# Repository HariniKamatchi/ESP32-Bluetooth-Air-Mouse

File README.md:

# ESP32-Based Bluetooth Air Mouse Using MPU6050

A gesture-controlled wireless air mouse developed using an ESP32 microcontroller and MPU6050 motion sensor. The project explores an alternative approach to traditional computer input devices by translating hand movements into cursor control.

## 1. Project Overview

The Air Mouse is an embedded system designed to enable computer interaction through hand gestures rather than a conventional physical mouse.

The system uses the MPU6050, which integrates a 3-axis accelerometer and a 3-axis gyroscope, to capture hand movement and orientation. The ESP32 processes the sensor readings and supports wireless communication with a host computer.

An LDR-based input mechanism is also incorporated to detect gesture-based clicking.

The project combines motion sensing, embedded programming, wireless communication and custom PCB development to demonstrate gesture-based human-computer interaction.

## 2. Key Features

- Gesture-based cursor movement using MPU6050.
- ESP32-based embedded processing.
- 3-axis accelerometer and gyroscope data acquisition.
- I2C communication between ESP32 and MPU6050.
- LDR-based click detection.
- Serial data transmission for host-side visualization.
- Custom PCB design using KiCad.
- Compact and portable hardware architecture.

## 3. Hardware Components

| Component | Function |
|---|---|
| ESP32 Development Board | Main microcontroller |
| MPU6050 | Motion and orientation sensing |
| LDR | Gesture-based click detection |
| 56 kΩ Resistor | LDR voltage divider |
| Li-ion Battery | Portable power supply |
| TP4056 Module | Battery charging |
| Perfboard | Initial hardware implementation |
| Custom PCB | Hardware integration |

## 4. Software and Tools

- Arduino IDE
- Embedded C/C++
- Processing IDE
- KiCad PCB Design Suite
- Adafruit MPU6050 Library
- Adafruit Unified Sensor Library
- Wire Library
- Processing Serial Library

## 5. System Architecture

The system consists of three primary stages:

**1. Motion Sensing**

The MPU6050 captures hand movements and orientation using its accelerometer and gyroscope.

**2. Data Acquisition and Processing**

The ESP32 reads the sensor values through the I2C interface. Gyroscope readings are scaled to generate cursor movement values. The LDR input is used to determine the click state.

**3. Host-Side Visualization**

The ESP32 transmits the processed values through serial communication. A Processing application receives the data and visualizes cursor movement, click status and LDR readings.

### Data Communication Format

The ESP32 sends the following comma-separated data:

`gx,gy,click,ldrValue`

The data is transmitted at 115200 baud with a 50 ms sampling delay.

## 6. PCB Design

A custom Printed Circuit Board (PCB) was designed using **KiCad** to organize and integrate the electronic components.

The PCB design files are included in the repository.

The PCB development work includes:

- Circuit schematic design.
- PCB layout and routing.
- Component placement.
- Track routing and connectivity.
- PCB design visualization.

The repository includes the updated circular PCB layout. The earlier rectangular PCB design is documented in the original project report.

## 7. Repository Structure

```text
ESP32-Bluetooth-Air-Mouse/
│
├── Firmware/
│   └── Air_Mouse_ESP32.ino
│
├── Processing/
│   └── Air_Mouse_Processing.pde
│
├── PCB_Design/
│   ├── airmouse_embedded.kicad_pro
│   ├── airmouse_embedded.kicad_pcb
│   ├── airmouse_embedded.kicad_sch
│   ├── airmouse_embedded.net
│   └── README.md
│
├── Hardware/
│
├── Images/
│
├── Documentation/
│
├── README.md
└── LICENSE
```

## 8. Getting Started

### ESP32 Firmware Setup

1. Install Arduino IDE.
2. Install ESP32 board support.
3. Install the Adafruit MPU6050 and Adafruit Unified Sensor libraries.
4. Open `Firmware/Air_Mouse_ESP32.ino`.
5. Connect the MPU6050 and LDR to the ESP32.
6. Select the appropriate ESP32 board and COM port.
7. Upload the firmware.

### Processing Setup

1. Install Processing IDE.
2. Open `Processing/Air_Mouse_Processing.pde`.
3. Change `COM3` to the serial port assigned to your ESP32, if required.
4. Ensure the Arduino Serial Monitor is closed.
5. Run the Processing sketch.

The Processing application displays a simulated cursor inside a 500 × 500 window, along with the click state and LDR readings.

### KiCad Project Setup

1. Install KiCad.
2. Navigate to the `PCB_Design/` directory.
3. Open `airmouse_embedded.kicad_pro`.
4. View or modify the circuit schematic and PCB layout.

## 9. Applications

- Wireless presentation control.
- Gesture-based computer interaction.
- Smart device and media control.
- Interactive gaming interfaces.
- Virtual reality interaction.
- Assistive human-computer interaction.

## 10. Future Improvements

- Improved motion calibration and filtering.
- Advanced gesture recognition.
- Reduced sensor drift and improved cursor sensitivity.
- Rechargeable battery integration.
- Low-power operation.
- Ergonomic enclosure development.
- Expanded gesture-based controls.

**Institution:** Vellore Institute of Technology, Chennai  
**Department:** Electronics and Communication Engineering  
**Course:** BECE403E – Embedded System Design  
**Project Year:** 2025

## 11. License

This project is licensed under the MIT License. See the `LICENSE` file for details.

---

*Exploring the intersection of embedded systems, motion sensing, wireless communication and human-computer interaction.*

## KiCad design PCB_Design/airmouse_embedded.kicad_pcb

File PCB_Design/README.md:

# KiCad PCB Design

This directory contains the editable KiCad project files for the Air Mouse PCB.

## Included files

- `airmouse_embedded.kicad_pro` - KiCad project settings
- `airmouse_embedded.kicad_sch` - circuit schematic
- `airmouse_embedded.kicad_pcb` - PCB layout
- `airmouse_embedded.net` - exported netlist

Open `airmouse_embedded.kicad_pro` in KiCad to work with the project.

Temporary lock files (`*.lck`), local project state (`*.kicad_prl`), and the local footprint information cache are intentionally excluded. KiCad can regenerate these local files when the project is opened.

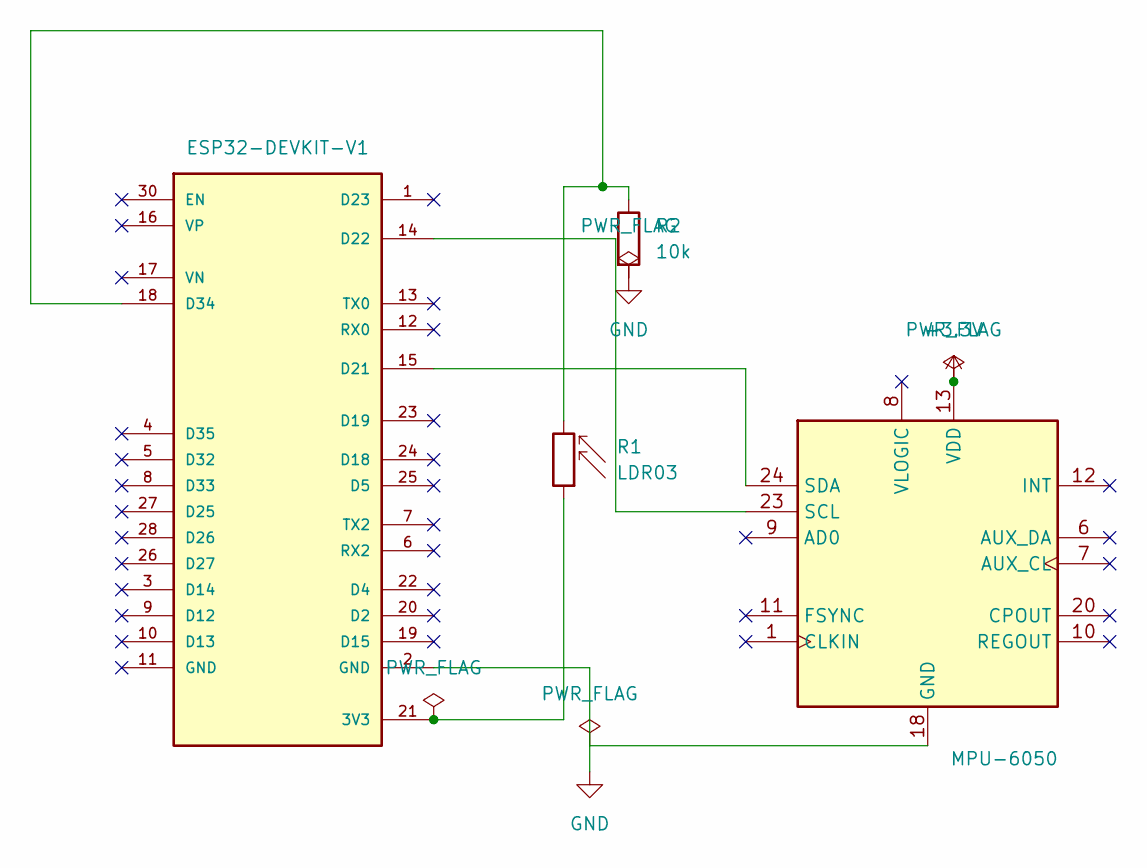
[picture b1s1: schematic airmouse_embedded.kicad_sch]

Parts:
R1: LDR03; R_LDR_10x8.5mm_P7.6mm_Vertical
R2: 10k; R_Axial_DIN0617_L17.0mm_D6.0mm_P20.32mm_Horizontal
U1: MPU-6050; QFN50P400X400X95-24N
U3: ESP32-DEVKIT-V1; MODULE_ESP32_DEVKIT_V1; PARTREV N/A

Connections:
+3.3V: U1.13 (VDD)
GND: R2.2, U3.2 (GND)
unnamed: U1.23 (SCL), U3.14 (D22)
unnamed: U1.24 (SDA), U3.15 (D21)
unnamed: R1.1, U3.21 (3V3)
unnamed: R1.2, R2.1, U3.18 (D34)

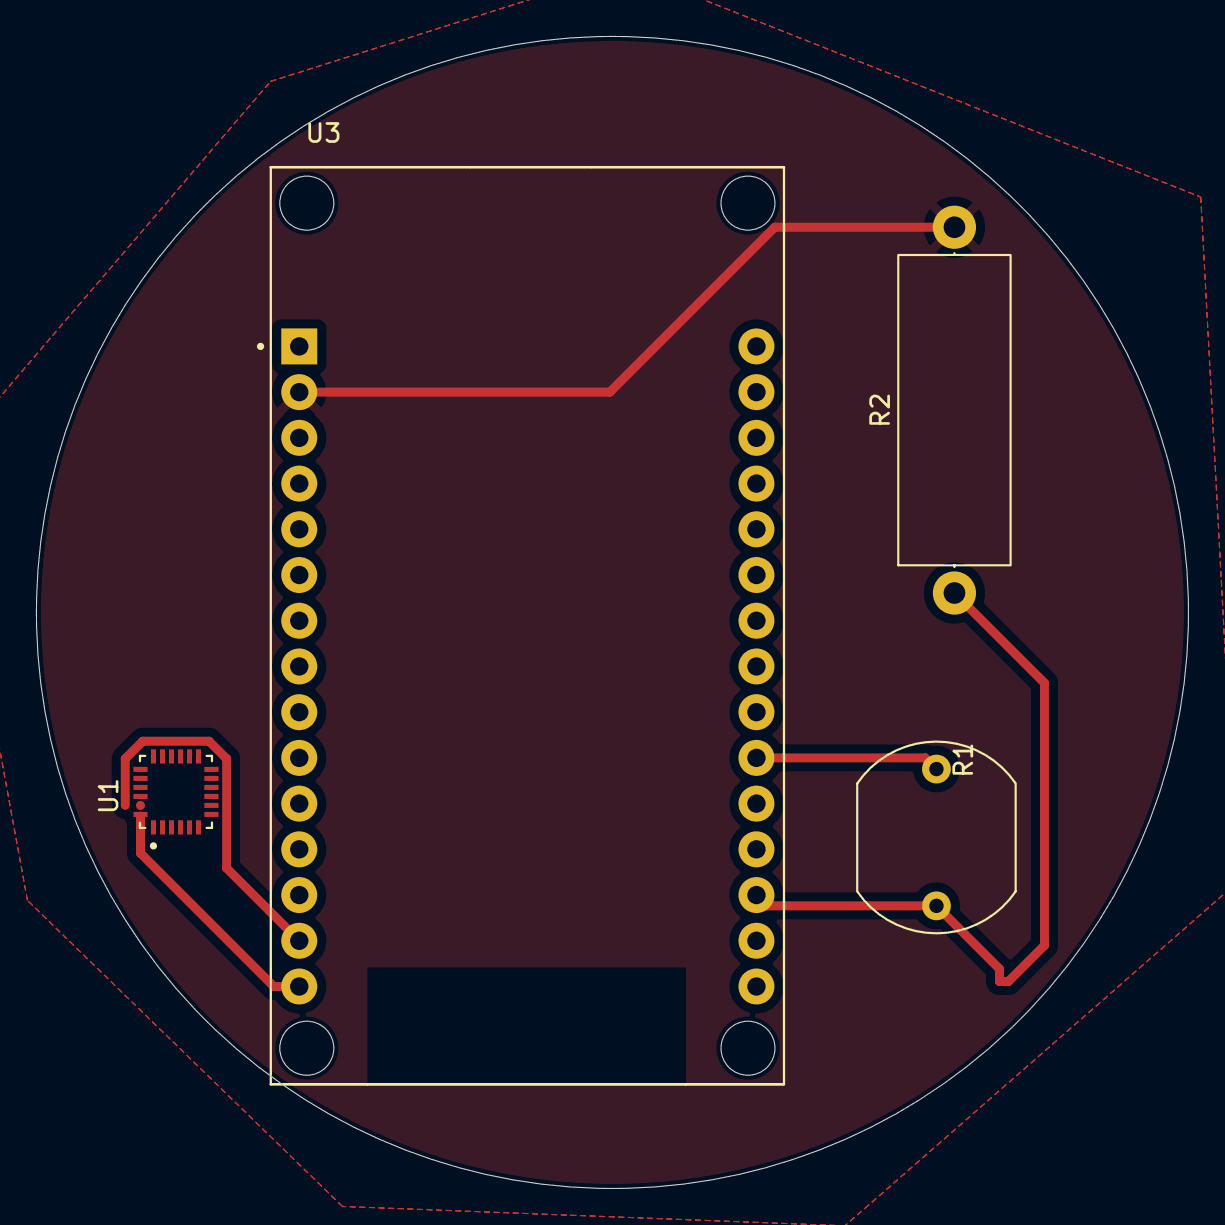
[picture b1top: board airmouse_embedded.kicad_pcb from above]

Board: 2 copper layers, 64.0 x 64.0 mm, 4 parts (0 on the bottom side), 5 nets.
